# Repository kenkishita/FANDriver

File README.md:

# FANDriver - it is able to drive a fan.
Inputs : VCC, PWM, GND
When using with RAMPS, I recoomend VCC=12V, PWM by SERVO ports or AUX...
PWM high level >=5V

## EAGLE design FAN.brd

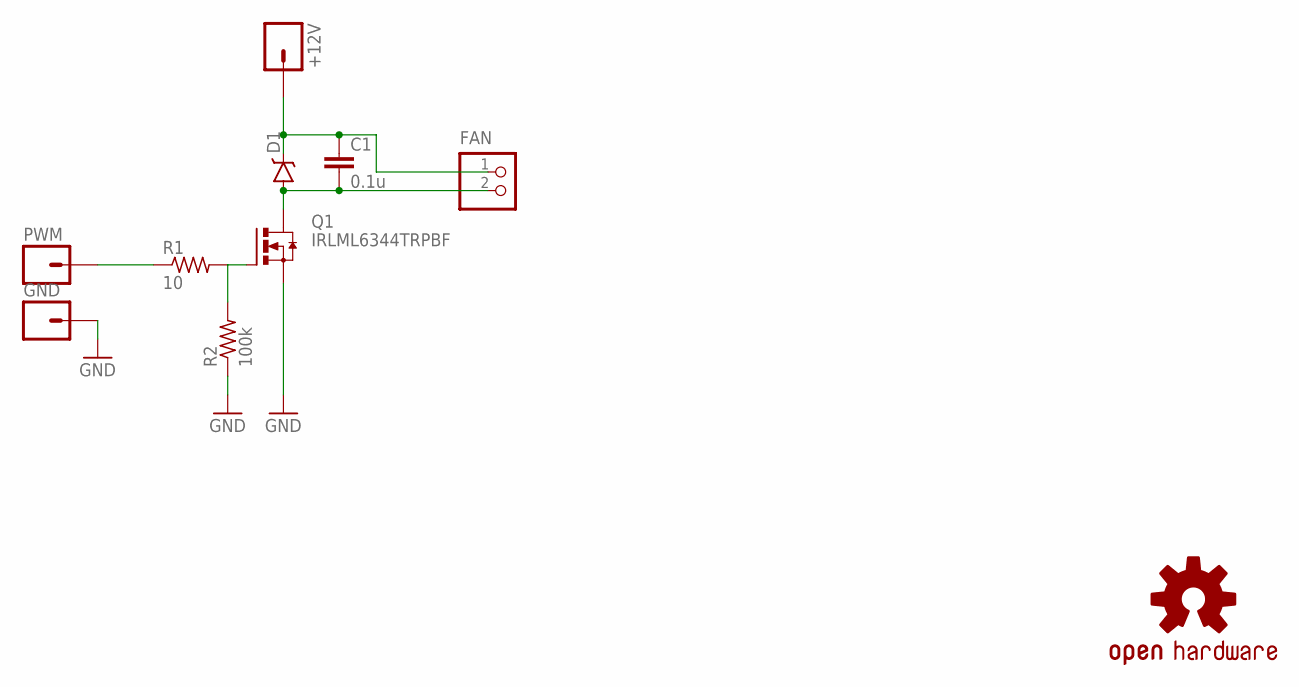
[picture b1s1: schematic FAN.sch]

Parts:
+12V: M01PTH; 1X01
C1: 0.1u; 0603-CAP
D1: DIODE-SCHOTTKY; TUMD2
FAN: S2B-XH-A
GND: M01PTH; 1X01
PWM: M01PTH; 1X01
Q1: IRLML6344TRPBF; SOT-23-3
R1: 10; 1608
R2: 100k; 1608
U$1: OSHW-LOGOS; OSHW-LOGO-S

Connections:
+12V: +12V.1, C1.1, D1.C, FAN.1
FAN: C1.2, D1.A, FAN.2, Q1.3 (D)
GND: GND.1, Q1.2 (S), R2.P$1 (1)
unnamed: PWM.1, R1.P$1 (1)
unnamed: Q1.1 (G), R1.P$2 (2), R2.P$2 (2)

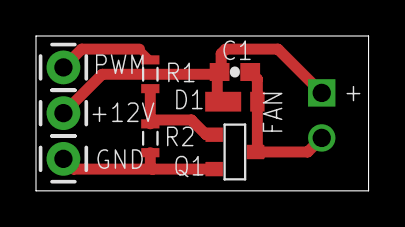
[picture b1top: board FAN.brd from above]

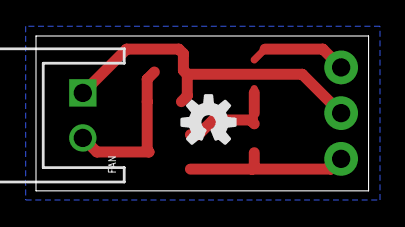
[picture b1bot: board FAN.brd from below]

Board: 2 copper layers, 18.5 x 8.6 mm, 10 parts (2 on the bottom side), 5 nets.

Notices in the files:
parts and their libraries:
SparkFun-Connectors: Licensing: Creative Commons ShareAlike 4.0 International - https://creativecommons.org/licenses/by-sa/4.0
SparkFun: Licensing: CC v3.0 Share-Alike You are welcome to use this library for commercial purposes.
